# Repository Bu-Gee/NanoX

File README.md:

See LICENSE file for license information.

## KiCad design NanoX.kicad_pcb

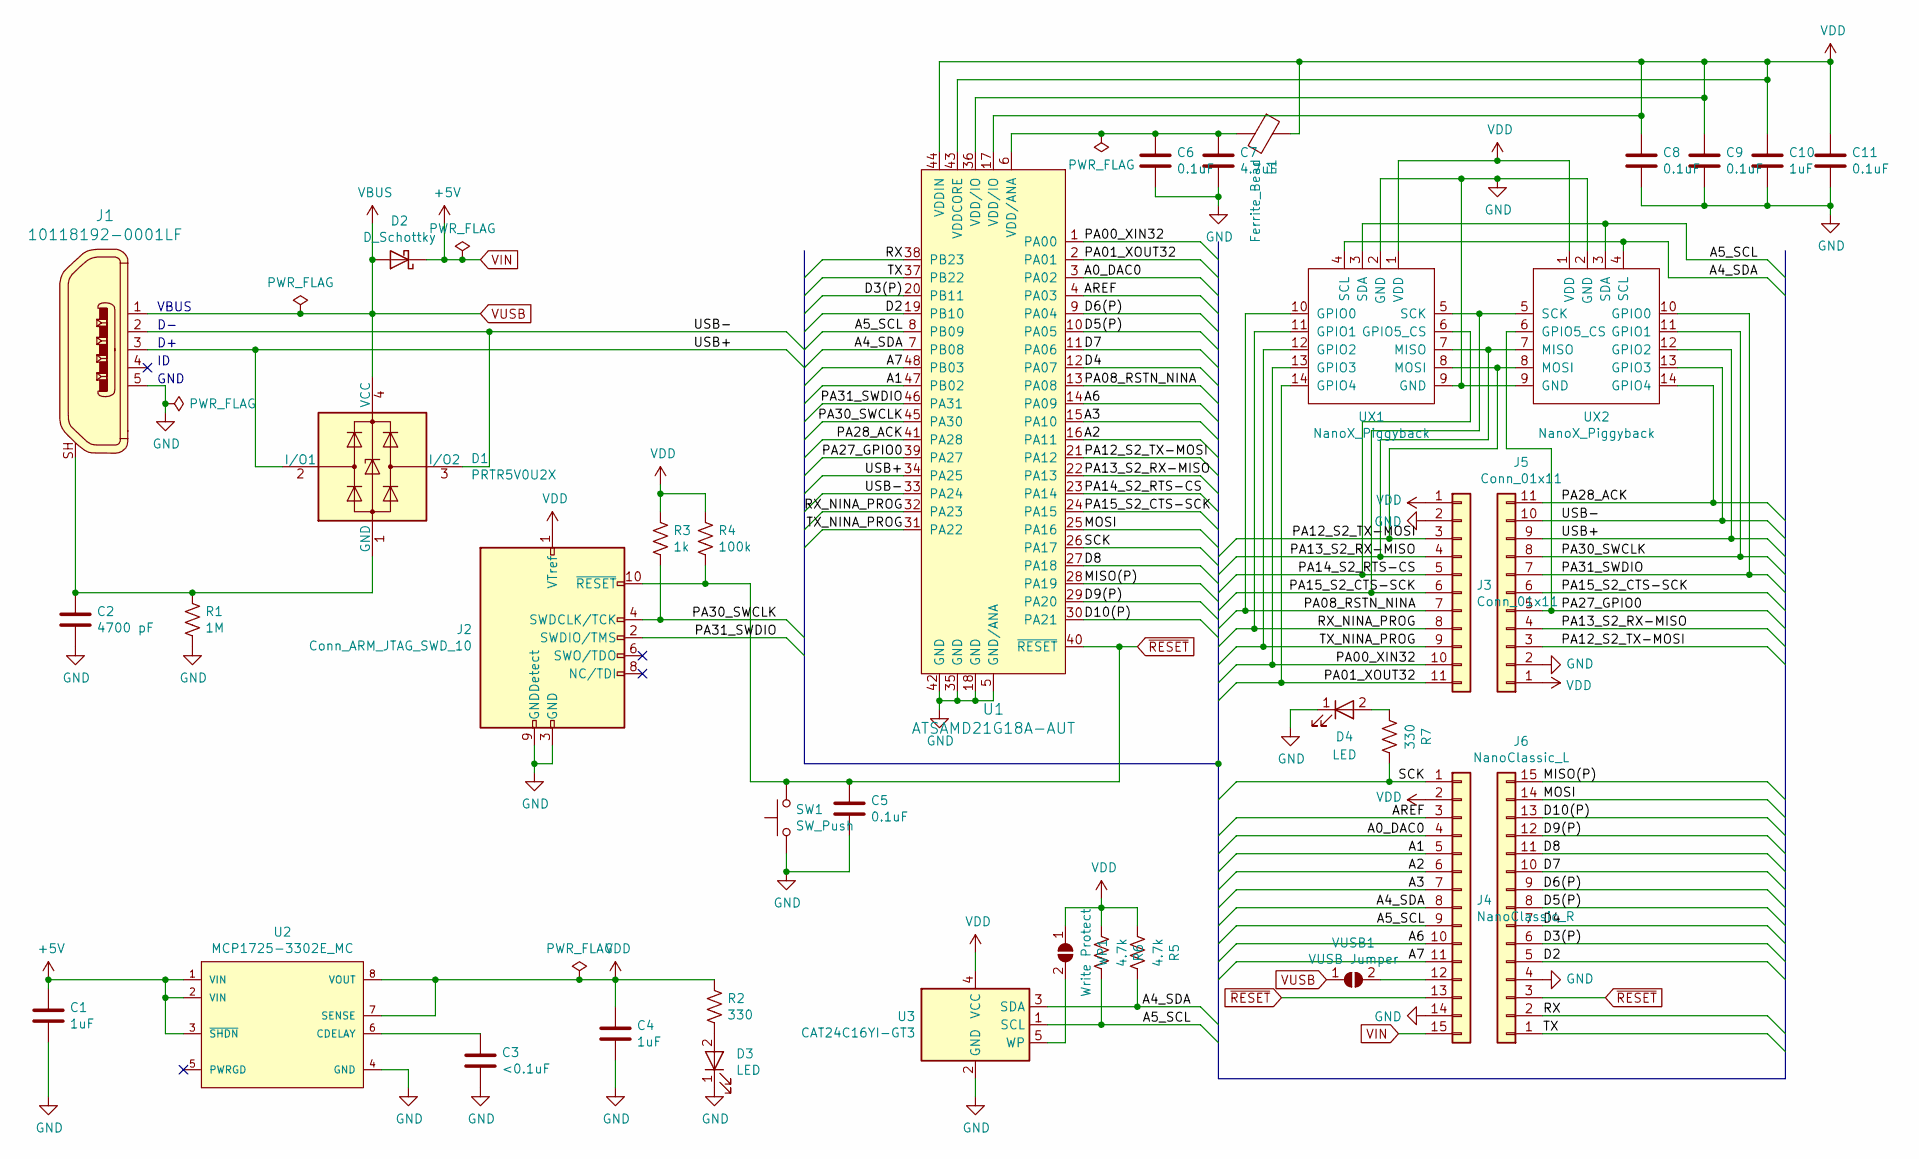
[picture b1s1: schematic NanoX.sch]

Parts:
C1, C4, C10: 1uF; C_0603_HandSoldering
C2: 4700 pF; C_0603_HandSoldering
C3: <0.1uF; C_0603_HandSoldering
C5, C6, C8, C9, C11: 0.1uF; C_0603_HandSoldering
C7: 4.7uF; C_0603_HandSoldering
D1: PRTR5V0U2X; SOT-143; Digikey 1727-3884-1-ND
D2: D_Schottky; D_0603; Digikey 641-1520-1-ND
D3, D4: LED; LED_0603_HandSoldering
J1: 10118192-0001LF; USB_Micro_B_Female_10118192; MPN 10118192-0001LF; Digi-Key_PN 609-4613-1-ND
J2: Conn_ARM_JTAG_SWD_10; Pin_Header_Straight_2x05_Pitch1.27mm; Digikey 1175-1627-ND
J3, J5: Conn_01x11; Pin_Header_Straight_1x11_Pitch2.54mm
J4: NanoClassic_R; Pin_Header_Straight_1x15_Pitch2.54mm
J6: NanoClassic_L; Pin_Header_Straight_1x15_Pitch2.54mm
L1: Ferrite_Bead; L_0603_HandSoldering
R1: 1M; R_0603_HandSoldering
R2, R7: 330; R_0603_HandSoldering
R3: 1k; R_0603_HandSoldering
R4: 100k; R_0603_HandSoldering
R5, R6: 4.7k; R_0603_HandSoldering
SW1: SW_Push; SW_SPST_EVQP2; Digikey P12298SCT-ND
U1: ATSAMD21G18A-AUT; TQFP-48_7x7mm; MPN ATSAMD21G18A-AUT; Digi-Key_PN ATSAMD21G18A-AUTCT-ND
U2: MCP1725-3302E_MC; DFN-8-1EP_3x2mm_P0.5mm_EP1.75x1.45mm; Digikey MCP1725-3302E/MC-ND
U3: CAT24C16YI-GT3; TSOT-23-5; Digikey CAT24C16YI-GT3CT-ND
UX1, UX2: NanoX_Piggyback
VUSB1: VUSB Jumper; SolderJumper-2_P1.3mm_Open_TrianglePad1.0x1.5mm
WP1: Write Protect; SolderJumper-2_P1.3mm_Open_TrianglePad1.0x1.5mm

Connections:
/A0_DAC0: J4.4, U1.3 (PA02)
/A1: J4.5, U1.47 (PB02)
/A2: J4.6, U1.16 (PA11)
/A3: J4.7, U1.15 (PA10)
/A4_SDA: J4.8, R5.1, U1.7 (PB08), U3.3 (SDA), UX1.4 (SCL), UX2.4 (SCL)
/A5_SCL: J4.9, R6.1, U1.8 (PB09), U3.1 (SCL), UX1.3 (SDA), UX2.3 (SDA)
/A6: J4.10, U1.14 (PA09)
/A7: J4.11, U1.48 (PB03)
/AREF: J4.3, U1.4 (PA03)
/D2: J6.5, U1.19 (PB10)
/D3(P): J6.6, U1.20 (PB11)
/D4: J6.7, U1.12 (PA07)
/D5(P): J6.8, U1.10 (PA05)
/D6(P): J6.9, U1.9 (PA04)
/D7: J6.10, U1.11 (PA06)
/D8: J6.11, U1.27 (PA18)
/D9(P): J6.12, U1.29 (PA20)
/D10(P): J6.13, U1.30 (PA21)
/MISO(P): J6.15, U1.28 (PA19)
/MOSI: J6.14, U1.25 (PA16)
/PA00_XIN32: J3.10, U1.1 (PA00), UX1.13 (GPIO3)
/PA01_XOUT32: J3.11, U1.2 (PA01), UX1.14 (GPIO4)
/PA08_RSTN_NINA: J3.7, U1.13 (PA08), UX1.10 (GPIO0)
/PA12_S2_TX-MOSI: J3.3, J5.3, U1.21 (PA12), UX1.8 (MOSI), UX2.8 (MOSI)
/PA13_S2_RX-MISO: J3.4, J5.4, U1.22 (PA13), UX1.7 (MISO), UX2.7 (MISO)
/PA14_S2_RTS-CS: J3.5, U1.23 (PA14), UX1.6 (GPIO5_CS)
/PA15_S2_CTS-SCK: J3.6, J5.6, U1.24 (PA15), UX1.5 (SCK), UX2.5 (SCK)
/PA27_GPIO0: J5.5, U1.39 (PA27), UX2.6 (GPIO5_CS)
/PA28_ACK: J5.11, U1.41 (PA28), UX2.14 (GPIO4)
/PA30_SWCLK: J2.4 (SWDCLK/TCK), J5.8, R3.2, U1.45 (PA30), UX2.11 (GPIO1)
/PA31_SWDIO: J2.2 (SWDIO/TMS), J5.7, U1.46 (PA31), UX2.10 (GPIO0)
/RX: J6.2, U1.38 (PB23)
/RX_NINA_PROG: J3.8, U1.32 (PA23), UX1.11 (GPIO1)
/SCK: J4.1, R7.1, U1.26 (PA17)
/TX: J6.1, U1.37 (PB22)
/TX_NINA_PROG: J3.9, U1.31 (PA22), UX1.12 (GPIO2)
/USB+: D1.2 (I/O1), J1.3, J5.9, U1.34 (PA25), UX2.12 (GPIO2)
/USB-: D1.3 (I/O2), J1.2, J5.10, U1.33 (PA24), UX2.13 (GPIO3)
GND: C1.2, C2.2, C3.2, C4.2, C5.2, C6.2, C7.2, C8.2, C9.2, C10.2, C11.2, D3.1 (K), D4.1 (K), J1.5, J2.3 (GND), J2.5 (GND), J2.9 (GNDDetect), J3.2, J4.14, J5.2, J6.4, R1.2, SW1.1, U1.5 (GND/ANA), U1.18 (GND), U1.35 (GND), U1.42 (GND), U2.4 (GND), U2.9, U3.2 (GND), UX1.2 (GND), UX1.9 (GND), UX2.2 (GND), UX2.9 (GND)
unnamed: C2.1, D1.1 (GND), J1.SH, R1.1
unnamed: C3.1, U2.6 (CDELAY)
unnamed: C6.1, C7.1, L1.2, U1.6 (VDD/ANA)
unnamed: D3.2 (A), R2.2
unnamed: D4.2 (A), R7.2
unnamed: J4.12, VUSB1.2 (B)
unnamed: U3.5 (WP), WP1.2 (B)
VDD: C4.1, C8.1, C9.1, C10.1, C11.1, J2.1 (VTref), J3.1, J4.2, J5.1, L1.1, R2.1, R3.1, R4.1, R5.2, R6.2, U1.17 (VDD/IO), U1.36 (VDD/IO), U1.43 (VDDCORE), U1.44 (VDDIN), U2.7 (SENSE), U2.8 (VOUT), U3.4 (VCC), UX1.1 (VDD), UX2.1 (VDD), WP1.1 (A)
VIN: C1.1, D2.1 (K), J4.15, U2.1 (VIN), U2.2 (VIN), U2.3 (~SHDN~)
VUSB: D1.4 (VCC), D2.2 (A), J1.1, VUSB1.1 (A)
~RESET: C5.1, J2.10 (~RESET~), J4.13, J6.3, R4.2, SW1.2, U1.40 (~RESET)

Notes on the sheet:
VBUS
GND

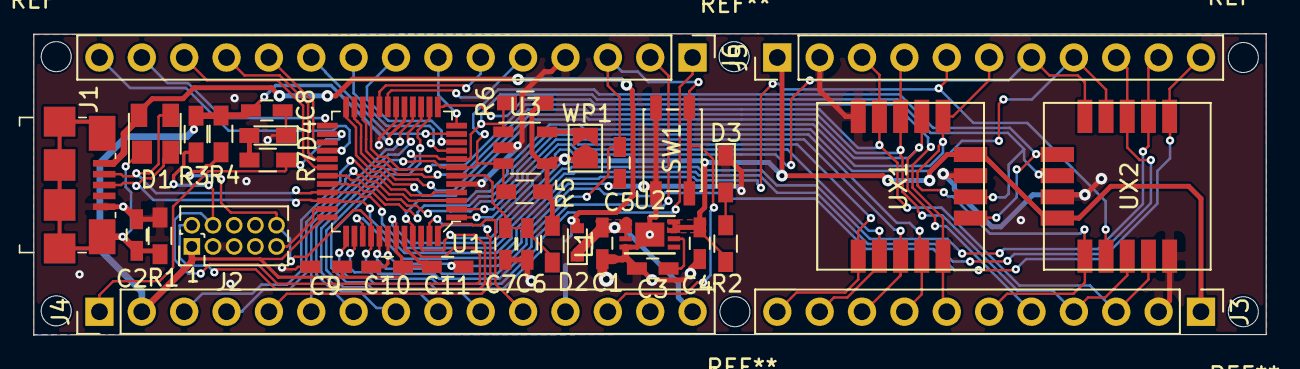
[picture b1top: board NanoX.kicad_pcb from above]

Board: 2 copper layers, 73.9 x 18.1 mm, 37 parts (1 on the bottom side), 50 nets.

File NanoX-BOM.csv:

"Source:","/home/bu/KiCAD/NanoX/NanoX/NanoX.sch"
"Date:","Tue 29 Sep 2020 12:23:44 EDT"
"Tool:","Eeschema 5.1.5"
"Generator:","/home/bu/KiCAD/plugins/bom_csv_grouped_by_value_with_fp_digikey.py"
"Component Count:","37"
"Ref","Qnty","Value","Cmp name","Footprint","Description","Vendor","Digikey PN"
"C1, C4, C10, ","3","1uF","C","Capacitors_SMD:C_0603_HandSoldering","Unpolarized capacitor","",""
"C2, ","1","4700 pF","C","Capacitors_SMD:C_0603_HandSoldering","Unpolarized capacitor","",""
"C3, ","1","<0.1uF","C","Capacitors_SMD:C_0603_HandSoldering","Unpolarized capacitor","",""
"C5, C6, C8, C9, C11, ","5","0.1uF","C","Capacitors_SMD:C_0603_HandSoldering","Unpolarized capacitor","",""
"C7, ","1","4.7uF","C","Capacitors_SMD:C_0603_HandSoldering","Unpolarized capacitor","",""
"D1, ","1","PRTR5V0U2X","PRTR5V0U2X","TO_SOT_Packages_SMD:SOT-143","Ultra low capacitance double rail-to-rail ESD protection diode, SOT-363","","1727-3884-1-ND"
"D2, ","1","D_Schottky","D_Schottky","Diodes_SMD:D_0603","Schottky diode","","641-1520-1-ND"
"D3, D4, ","2","LED","LED","LEDs:LED_0603_HandSoldering","LED generic","",""
"J1, ","1","10118192-0001LF","10118192-0001LF","digikey-footprints:USB_Micro_B_Female_10118192","CONN RCPT USB2.0 MICRO B SMD R/A","","609-4613-1-ND"
"J2, ","1","Conn_ARM_JTAG_SWD_10","Conn_ARM_JTAG_SWD_10","Pin_Headers:Pin_Header_Straight_2x05_Pitch1.27mm","Cortex Debug Connector, standard ARM Cortex-M SWD and JTAG interface","","1175-1627-ND"
"J3, J5, ","2","Conn_01x11","Conn_01x11","Pin_Headers:Pin_Header_Straight_1x11_Pitch2.54mm","Generic connector, single row, 01x11","",""
"J4, ","1","NanoClassic_R","Conn_01x15","Pin_Headers:Pin_Header_Straight_1x15_Pitch2.54mm","Generic connector, single row, 01x15","",""
"J6, ","1","NanoClassic_L","Conn_01x15","Pin_Headers:Pin_Header_Straight_1x15_Pitch2.54mm","Generic connector, single row, 01x15","",""
"L1, ","1","Ferrite_Bead","Ferrite_Bead","Inductors_SMD:L_0603_HandSoldering","Ferrite bead","",""
"R1, ","1","1M","R_US","Resistors_SMD:R_0603_HandSoldering","Resistor, US symbol","",""
"R2, R7, ","2","330","R_US","Resistors_SMD:R_0603_HandSoldering","Resistor, US symbol","",""
"R3, ","1","1k","R_US","Resistors_SMD:R_0603_HandSoldering","Resistor, US symbol","",""
"R4, ","1","100k","R_US","Resistors_SMD:R_0603_HandSoldering","Resistor, US symbol","",""
"R5, R6, ","2","4.7k","R_US","Resistors_SMD:R_0603_HandSoldering","Resistor, US symbol","",""
"SW1, ","1","SW_Push","SW_Push","Buttons_Switches_SMD:SW_SPST_EVQP2","Push button switch, generic, two pins","","P12298SCT-ND"
"U1, ","1","ATSAMD21G18A-AUT","ATSAMD21G18A-AUT","digikey-footprints:TQFP-48_7x7mm","IC MCU 32BIT 256KB FLASH 48TQFP","","ATSAMD21G18A-AUTCT-ND"
"U2, ","1","MCP1725-3302E_MC","MCP1725-1202E_SN","Package_DFN_QFN:DFN-8-1EP_3x2mm_P0.5mm_EP1.75x1.45mm","MCP1725-1202E/SN","","MCP1725-3302E/MC-ND"
"U3, ","1","CAT24C16YI-GT3","AT24CS02-STUM","TO_SOT_Packages_SMD:TSOT-23-5","I2C Serial EEPROM, 2Kb (256x8) with Unique Serial Number, SOT-23-5","","CAT24C16YI-GT3CT-ND"
"UX1, UX2, ","2","NanoX_Piggyback","NanoX_Piggyback","Bu:NanoX_Piggyback","","",""
"VUSB1, ","1","VUSB Jumper","SolderJumper_2_Open","Jumper:SolderJumper-2_P1.3mm_Open_TrianglePad1.0x1.5mm","Solder Jumper, 2-pole, open","",""
"WP1, ","1","Write Protect","SolderJumper_2_Open","Jumper:SolderJumper-2_P1.3mm_Open_TrianglePad1.0x1.5mm","Solder Jumper, 2-pole, open","",""

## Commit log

2020-09-28 Initial commit - Rev P1
2020-09-28 Add licensing info.
2020-09-28 Add Github link, remove bak file.
2020-09-28 Regenerate Gerbers after adding URL
2020-09-28 Rework pads, add Digikey part numbers.
2020-09-28 Regenerate Gerbers.
2020-09-28 Regenerate with fills rerun.
2020-09-29 Add Digikey part numbers and add them to BOM.
2020-09-29 Update Digikey part numbers.
2020-10-04 Add initial solder stencil 3D printable.
2020-10-25 Make new rimmed stencil
2020-10-25 Change pin 3 of MCP1725 to Vin instead of GND.
2020-10-25 Bump revision to P2.

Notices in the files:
NanoX.kicad_pcb:
Copyright(c) 2020, Fortian Inc.
Licensed Under CC-BY-NC-SA 3.0
